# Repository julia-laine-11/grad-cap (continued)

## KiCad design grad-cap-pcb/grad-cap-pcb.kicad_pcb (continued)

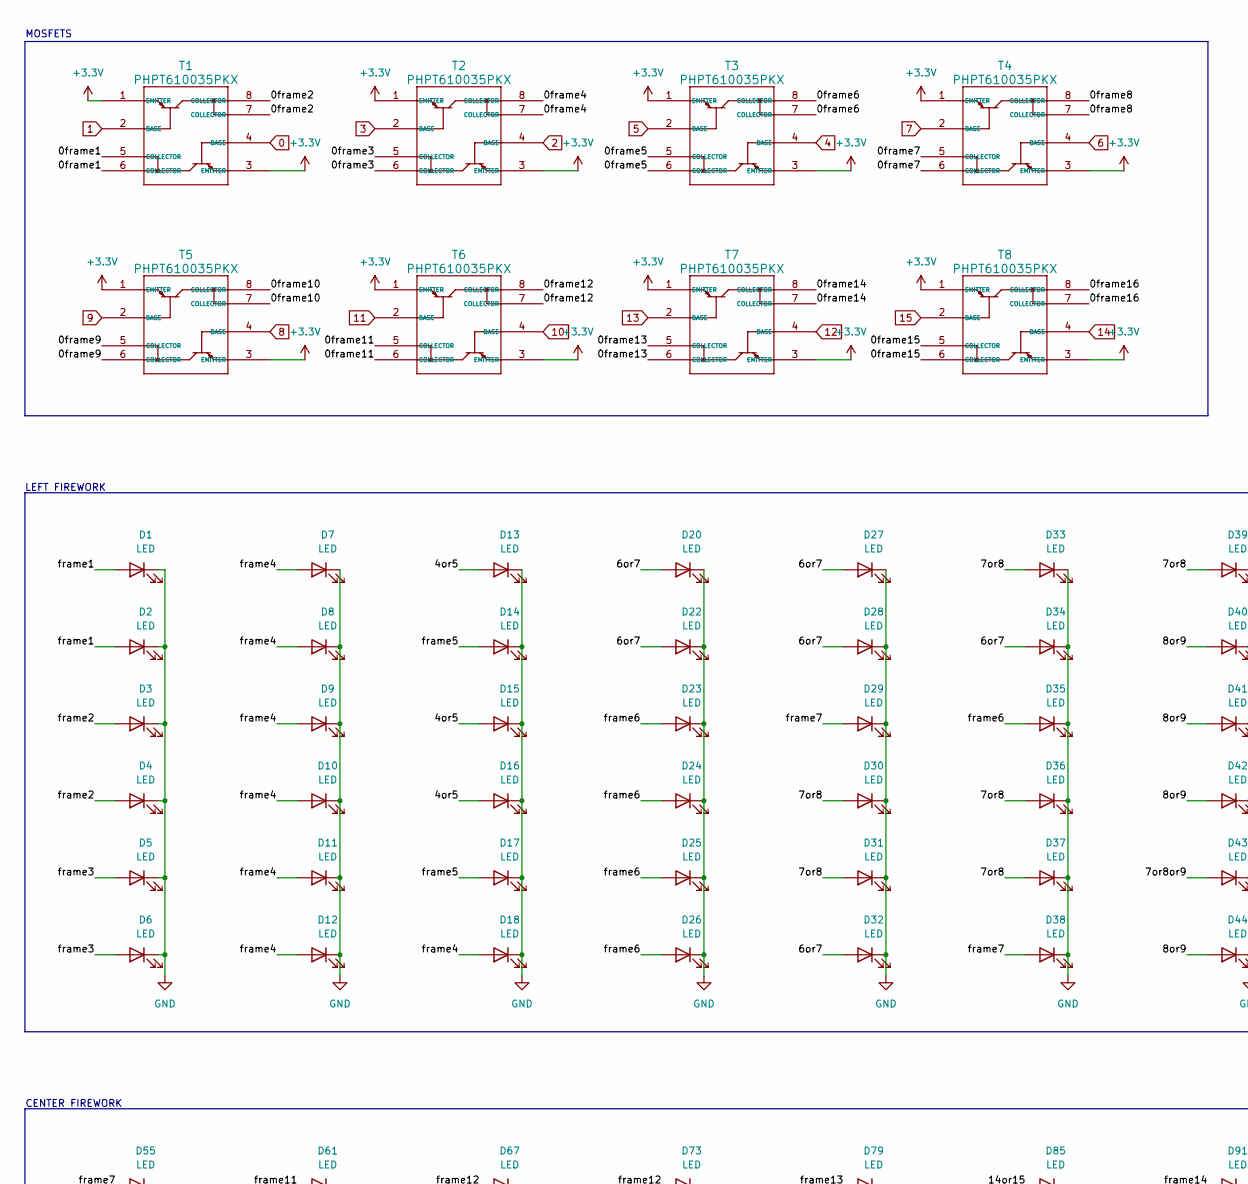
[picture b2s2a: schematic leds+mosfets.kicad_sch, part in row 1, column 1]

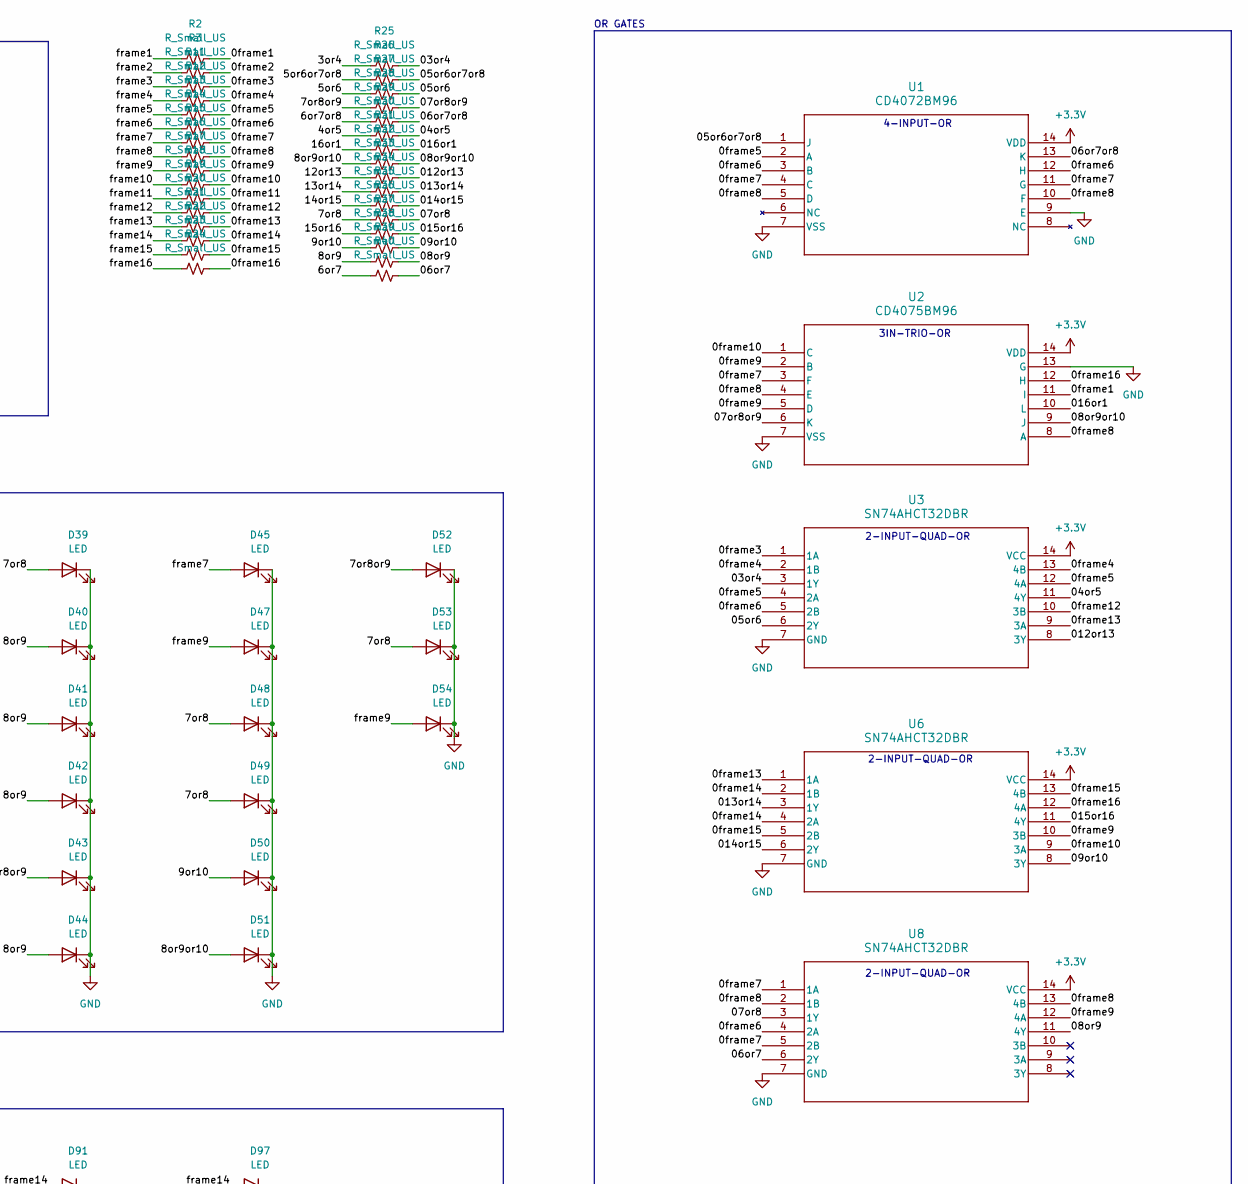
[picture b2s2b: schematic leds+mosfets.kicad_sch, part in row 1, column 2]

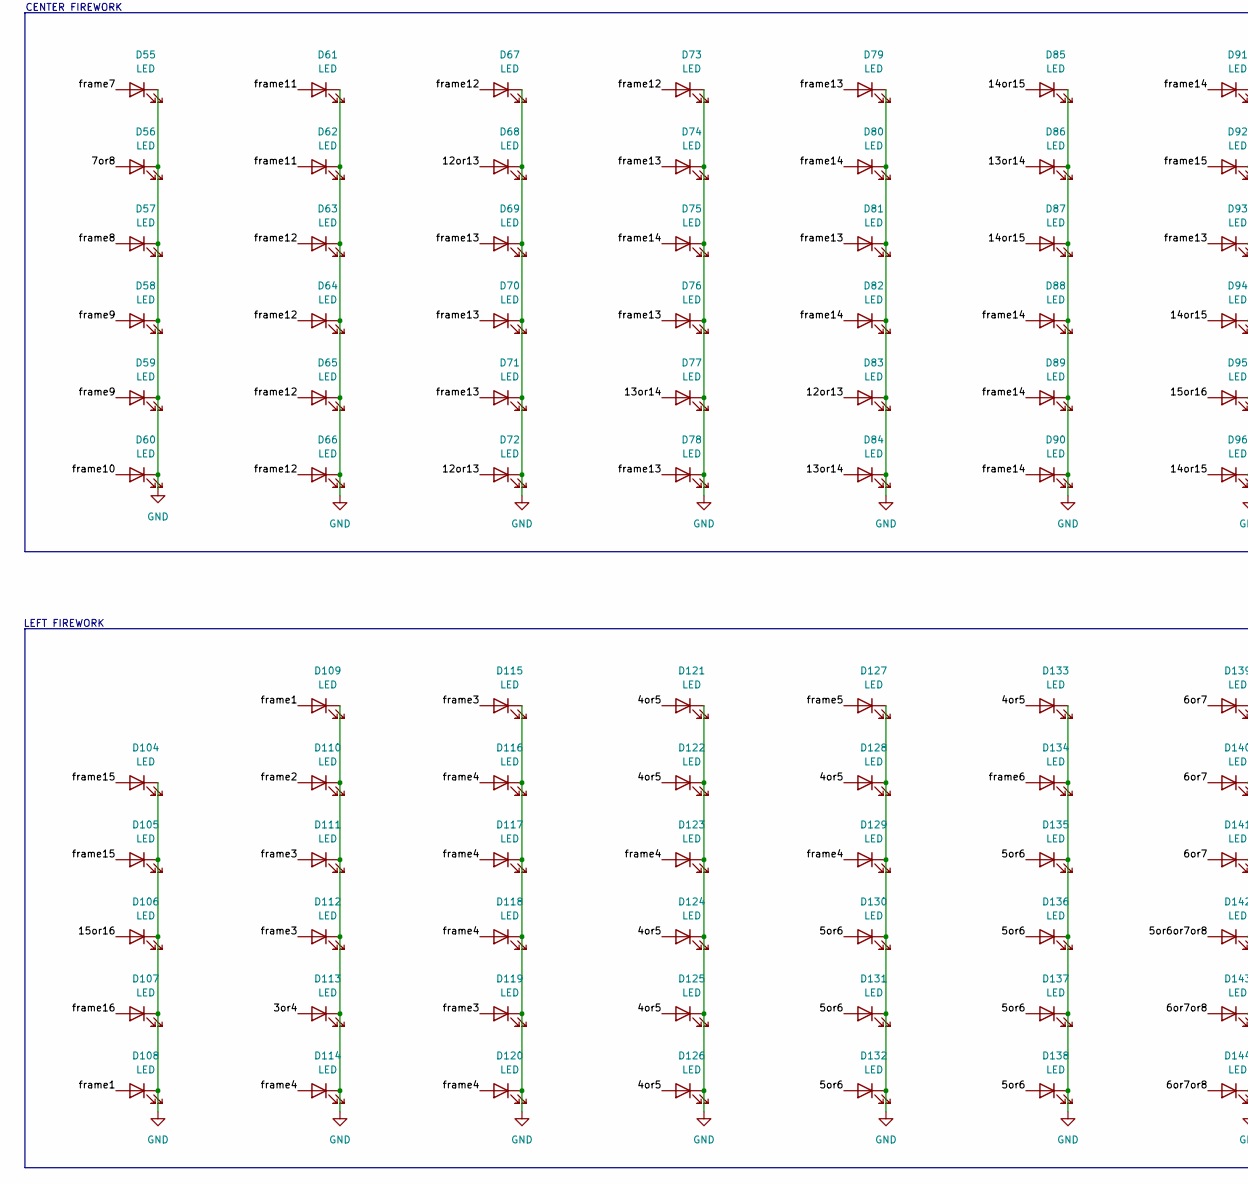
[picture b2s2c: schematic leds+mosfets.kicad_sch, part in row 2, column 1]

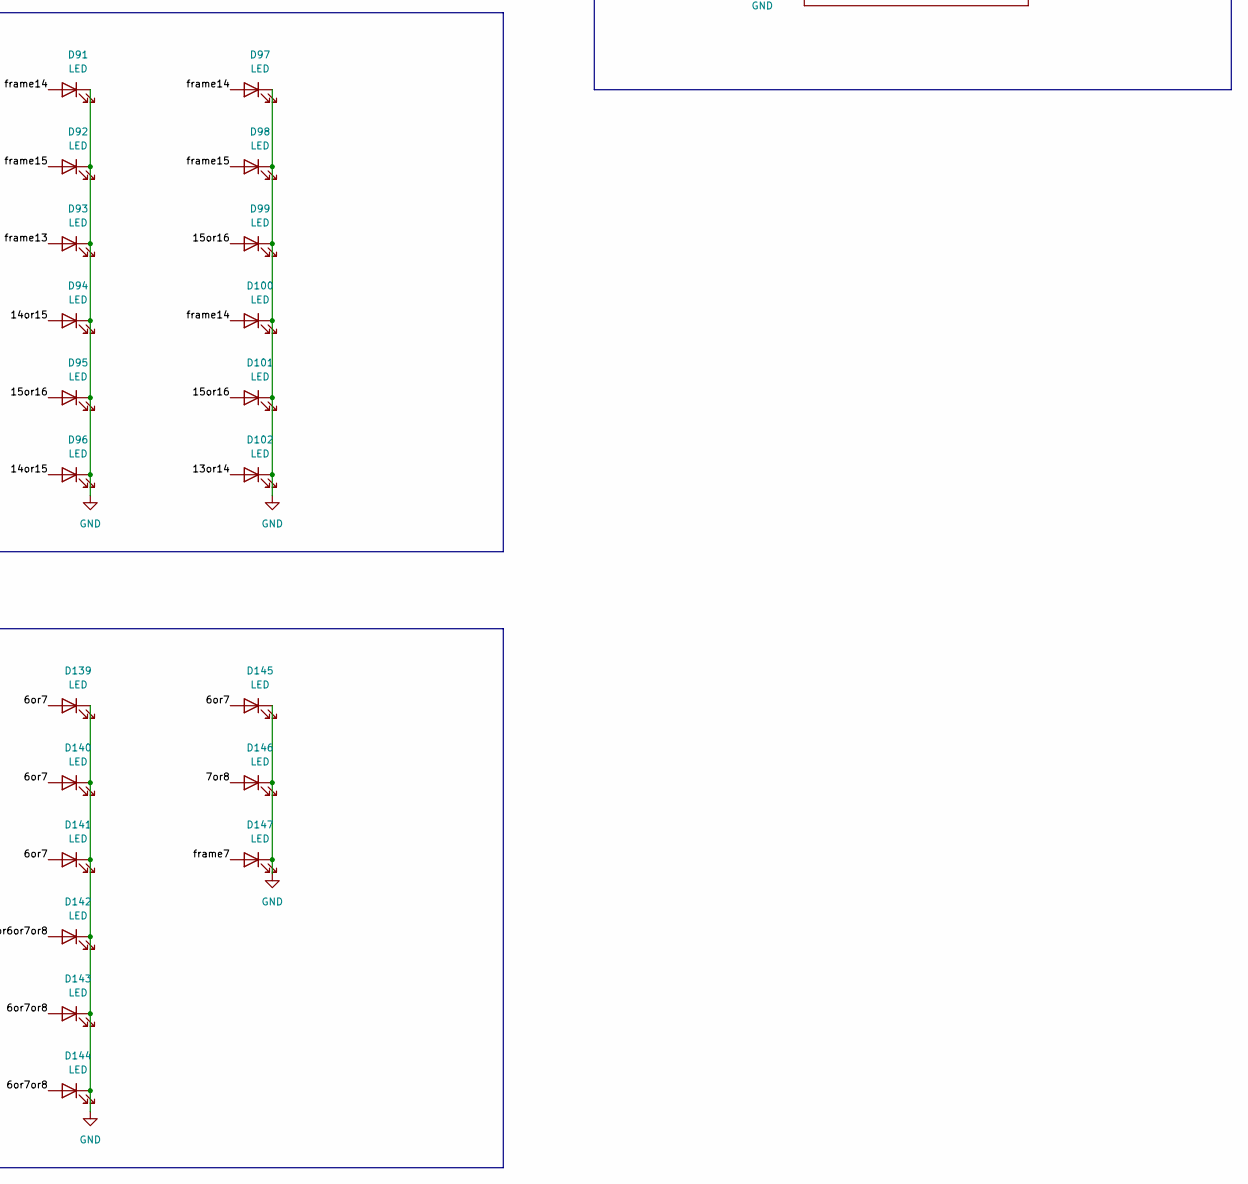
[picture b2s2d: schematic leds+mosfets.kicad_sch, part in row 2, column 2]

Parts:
D1, D2, D3, D4, D5, D6, D7, D8, D9, D10, D11, D12, D13, D14, D15, D16, D17, D18, D20, D22, D23, D24, D25, D26, D27, D28, D29, D30, D31, D32, D33, D34, D35, D36, D37, D38, D39, D40, D41, D42, D43, D44, D45, D47, D48, D49, D50, D51, D52, D53, D54, D55, D56, D57, D58, D59, D60, D61, D62, D63, D64, D65, D66, D67, D68, D69, D70, D71, D72, D73, D74, D75, D76, D77, D78, D79, D80, D81, D82, D83, D84, D85, D86, D87, D88, D89, D90, D91, D92, D93, D94, D95, D96, D97, D98, D99, D100, D101, D102, D104, D105, D106, D107, D108, D109, D110, D111, D112, D113, D114, D115, D116, D117, D118, D119, D120, D121, D122, D123, D124, D125, D126, D127, D128, D129, D130, D131, D132, D133, D134, D135, D136, D137, D138, D139, D140, D141, D142, D143, D144, D145, D146, D147: LED; LED_0603_1608Metric
R2, R3, R11, R12, R13, R14, R15, R16, R17, R18, R19, R20, R21, R22, R23, R24, R25, R26, R27, R28, R29, R30, R31, R32, R33, R34, R35, R36, R37, R38, R39, R40: R_Small_US; R_0805_2012Metric_Pad1.20x1.40mm_HandSolder
T1, T2, T3, T4, T5, T6, T7, T8: PHPT610035PKX; PHPT610035PKX_TRANS-2PNP-100V-3A
U1: CD4072BM96; CD4072BM96_4-INPUT-OR
U2: CD4075BM96; CD4075BM96-3IN-TRIO-OR
U3, U6, U8: SN74AHCT32DBR; SN74AHCT32DBR_2-INPUT-QUAD-OR

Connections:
0: T1.4 (BASE); also elsewhere on the board
1: T1.2 (BASE); also elsewhere on the board
2: T2.4 (BASE); also elsewhere on the board
3: T2.2 (BASE); also elsewhere on the board
4: T3.4 (BASE); also elsewhere on the board
5: T3.2 (BASE); also elsewhere on the board
6: T4.4 (BASE); also elsewhere on the board
7: T4.2 (BASE); also elsewhere on the board
8: T5.4 (BASE); also elsewhere on the board
9: T5.2 (BASE); also elsewhere on the board
10: T6.4 (BASE); also elsewhere on the board
11: T6.2 (BASE); also elsewhere on the board
12: T7.4 (BASE); also elsewhere on the board
13: T7.2 (BASE); also elsewhere on the board
14: T8.4 (BASE); also elsewhere on the board
15: T8.2 (BASE); also elsewhere on the board
+3.3V: T1.1 (EMITTER), T1.3 (EMITTER), T2.1 (EMITTER), T2.3 (EMITTER), T3.1 (EMITTER), T3.3 (EMITTER), T4.1 (EMITTER), T4.3 (EMITTER), T5.1 (EMITTER), T5.3 (EMITTER), T6.1 (EMITTER), T6.3 (EMITTER), T7.1 (EMITTER), T7.3 (EMITTER), T8.1 (EMITTER), T8.3 (EMITTER), U1.14 (VDD), U2.14 (VDD), U3.14 (VCC), U6.14 (VCC), U8.14 (VCC); also elsewhere on the board
/leds+mosfets/0frame1: R2.2, T1.5 (COLLECTOR), T1.6 (COLLECTOR), U2.11 (I)
/leds+mosfets/0frame2: R3.2, T1.7 (COLLECTOR), T1.8 (COLLECTOR)
/leds+mosfets/0frame3: R11.2, T2.5 (COLLECTOR), T2.6 (COLLECTOR), U3.1 (1A)
/leds+mosfets/0frame4: R12.2, T2.7 (COLLECTOR), T2.8 (COLLECTOR), U3.2 (1B), U3.13 (4B)
/leds+mosfets/0frame5: R13.2, T3.5 (COLLECTOR), T3.6 (COLLECTOR), U1.2 (A), U3.4 (2A), U3.12 (4A)
/leds+mosfets/0frame6: R14.2, T3.7 (COLLECTOR), T3.8 (COLLECTOR), U1.3 (B), U1.12 (H), U3.5 (2B), U8.4 (2A)
/leds+mosfets/0frame7: R15.2, T4.5 (COLLECTOR), T4.6 (COLLECTOR), U1.4 (C), U1.11 (G), U2.3 (F), U8.1 (1A), U8.5 (2B)
/leds+mosfets/0frame8: R16.2, T4.7 (COLLECTOR), T4.8 (COLLECTOR), U1.5 (D), U1.10 (F), U2.4 (E), U2.8 (A), U8.2 (1B), U8.13 (4B)
/leds+mosfets/0frame9: R17.2, T5.5 (COLLECTOR), T5.6 (COLLECTOR), U2.2 (B), U2.5 (D), U6.10 (3B), U8.12 (4A)
/leds+mosfets/0frame10: R18.2, T5.7 (COLLECTOR), T5.8 (COLLECTOR), U2.1 (C), U6.9 (3A)
/leds+mosfets/0frame11: R19.2, T6.5 (COLLECTOR), T6.6 (COLLECTOR)
/leds+mosfets/0frame12: R20.2, T6.7 (COLLECTOR), T6.8 (COLLECTOR), U3.10 (3B)
/leds+mosfets/0frame13: R21.2, T7.5 (COLLECTOR), T7.6 (COLLECTOR), U3.9 (3A), U6.1 (1A)
/leds+mosfets/0frame14: R22.2, T7.7 (COLLECTOR), T7.8 (COLLECTOR), U6.2 (1B), U6.4 (2A)
/leds+mosfets/0frame15: R23.2, T8.5 (COLLECTOR), T8.6 (COLLECTOR), U6.5 (2B), U6.13 (4B)
/leds+mosfets/0frame16: R24.2, T8.7 (COLLECTOR), T8.8 (COLLECTOR), U2.12 (H), U6.12 (4A)
/leds+mosfets/3or4: D113.2 (A), R25.1
/leds+mosfets/03or4: R25.2, U3.3 (1Y)
/leds+mosfets/4or5: D13.2 (A), D15.2 (A), D16.2 (A), D121.2 (A), D122.2 (A), D124.2 (A), D125.2 (A), D126.2 (A), D128.2 (A), D133.2 (A), R30.1
/leds+mosfets/04or5: R30.2, U3.11 (4Y)
/leds+mosfets/5or6: D130.2 (A), D131.2 (A), D132.2 (A), D135.2 (A), D136.2 (A), D137.2 (A), D138.2 (A), R27.1
/leds+mosfets/05or6: R27.2, U3.6 (2Y)
/leds+mosfets/5or6or7or8: D142.2 (A), R26.1
/leds+mosfets/05or6or7or8: R26.2, U1.1 (J)
/leds+mosfets/6or7: D20.2 (A), D22.2 (A), D27.2 (A), D28.2 (A), D32.2 (A), D34.2 (A), D139.2 (A), D140.2 (A), D141.2 (A), D145.2 (A), R40.1
/leds+mosfets/06or7: R40.2, U8.6 (2Y)
/leds+mosfets/6or7or8: D143.2 (A), D144.2 (A), R29.1
/leds+mosfets/06or7or8: R29.2, U1.13 (K)
/leds+mosfets/7or8: D30.2 (A), D31.2 (A), D33.2 (A), D36.2 (A), D37.2 (A), D39.2 (A), D48.2 (A), D49.2 (A), D53.2 (A), D56.2 (A), D146.2 (A), R36.1
/leds+mosfets/07or8: R36.2, U8.3 (1Y)
/leds+mosfets/7or8or9: D43.2 (A), D52.2 (A), R28.1
/leds+mosfets/07or8or9: R28.2, U2.6 (K)
/leds+mosfets/8or9: D40.2 (A), D41.2 (A), D42.2 (A), D44.2 (A), R39.1
/leds+mosfets/08or9: R39.2, U8.11 (4Y)
/leds+mosfets/8or9or10: D51.2 (A), R32.1
/leds+mosfets/08or9or10: R32.2, U2.9 (J)
/leds+mosfets/9or10: D50.2 (A), R38.1
/leds+mosfets/09or10: R38.2, U6.8 (3Y)
/leds+mosfets/012or13: R33.2, U3.8 (3Y)
/leds+mosfets/12or13: D68.2 (A), D72.2 (A), D83.2 (A), R33.1
/leds+mosfets/13or14: D77.2 (A), D84.2 (A), D86.2 (A), D102.2 (A), R34.1
/leds+mosfets/013or14: R34.2, U6.3 (1Y)
/leds+mosfets/14or15: D85.2 (A), D87.2 (A), D94.2 (A), D96.2 (A), R35.1
/leds+mosfets/014or15: R35.2, U6.6 (2Y)
/leds+mosfets/15or16: D95.2 (A), D99.2 (A), D101.2 (A), D106.2 (A), R37.1
/leds+mosfets/015or16: R37.2, U6.11 (4Y)
/leds+mosfets/016or1: R31.2, U2.10 (L)
/leds+mosfets/16or1: R31.1
/leds+mosfets/frame1: D1.2 (A), D2.2 (A), D108.2 (A), D109.2 (A), R2.1
/leds+mosfets/frame2: D3.2 (A), D4.2 (A), D110.2 (A), R3.1
/leds+mosfets/frame3: D5.2 (A), D6.2 (A), D111.2 (A), D112.2 (A), D115.2 (A), D119.2 (A), R11.1
/leds+mosfets/frame4: D7.2 (A), D8.2 (A), D9.2 (A), D10.2 (A), D11.2 (A), D12.2 (A), D18.2 (A), D114.2 (A), D116.2 (A), D117.2 (A), D118.2 (A), D120.2 (A), D123.2 (A), D129.2 (A), R12.1
/leds+mosfets/frame5: D14.2 (A), D17.2 (A), D127.2 (A), R13.1
/leds+mosfets/frame6: D23.2 (A), D24.2 (A), D25.2 (A), D26.2 (A), D35.2 (A), D134.2 (A), R14.1
/leds+mosfets/frame7: D29.2 (A), D38.2 (A), D45.2 (A), D55.2 (A), D147.2 (A), R15.1
/leds+mosfets/frame8: D57.2 (A), R16.1
/leds+mosfets/frame9: D47.2 (A), D54.2 (A), D58.2 (A), D59.2 (A), R17.1
/leds+mosfets/frame10: D60.2 (A), R18.1
/leds+mosfets/frame11: D61.2 (A), D62.2 (A), R19.1
/leds+mosfets/frame12: D63.2 (A), D64.2 (A), D65.2 (A), D66.2 (A), D67.2 (A), D73.2 (A), R20.1
/leds+mosfets/frame13: D69.2 (A), D70.2 (A), D71.2 (A), D74.2 (A), D76.2 (A), D78.2 (A), D79.2 (A), D81.2 (A), D93.2 (A), R21.1
/leds+mosfets/frame14: D75.2 (A), D80.2 (A), D82.2 (A), D88.2 (A), D89.2 (A), D90.2 (A), D91.2 (A), D97.2 (A), D100.2 (A), R22.1
/leds+mosfets/frame15: D92.2 (A), D98.2 (A), D104.2 (A), D105.2 (A), R23.1
/leds+mosfets/frame16: D107.2 (A), R24.1
GND: D1.1 (K), D2.1 (K), D3.1 (K), D4.1 (K), D5.1 (K), D6.1 (K), D7.1 (K), D8.1 (K), D9.1 (K), D10.1 (K), D11.1 (K), D12.1 (K), D13.1 (K), D14.1 (K), D15.1 (K), D16.1 (K), D17.1 (K), D18.1 (K), D20.1 (K), D22.1 (K), D23.1 (K), D24.1 (K), D25.1 (K), D26.1 (K), D27.1 (K), D28.1 (K), D29.1 (K), D30.1 (K), D31.1 (K), D32.1 (K), D33.1 (K), D34.1 (K), D35.1 (K), D36.1 (K), D37.1 (K), D38.1 (K), D39.1 (K), D40.1 (K), D41.1 (K), D42.1 (K), D43.1 (K), D44.1 (K), D45.1 (K), D47.1 (K), D48.1 (K), D49.1 (K), D50.1 (K), D51.1 (K), D52.1 (K), D53.1 (K), D54.1 (K), D55.1 (K), D56.1 (K), D57.1 (K), D58.1 (K), D59.1 (K), D60.1 (K), D61.1 (K), D62.1 (K), D63.1 (K), D64.1 (K), D65.1 (K), D66.1 (K), D67.1 (K), D68.1 (K), D69.1 (K), D70.1 (K), D71.1 (K), D72.1 (K), D73.1 (K), D74.1 (K), D75.1 (K), D76.1 (K), D77.1 (K), D78.1 (K), D79.1 (K), D80.1 (K), D81.1 (K), D82.1 (K), D83.1 (K), D84.1 (K), D85.1 (K), D86.1 (K), D87.1 (K), D88.1 (K), D89.1 (K), D90.1 (K), D91.1 (K), D92.1 (K), D93.1 (K), D94.1 (K), D95.1 (K), D96.1 (K), D97.1 (K), D98.1 (K), D99.1 (K), D100.1 (K), D101.1 (K), D102.1 (K), D104.1 (K), D105.1 (K), D106.1 (K), D107.1 (K), D108.1 (K), D109.1 (K), D110.1 (K), D111.1 (K), D112.1 (K), D113.1 (K), D114.1 (K), D115.1 (K), D116.1 (K), D117.1 (K), D118.1 (K), D119.1 (K), D120.1 (K), D121.1 (K), D122.1 (K), D123.1 (K), D124.1 (K), D125.1 (K), D126.1 (K), D127.1 (K), D128.1 (K), D129.1 (K), D130.1 (K), D131.1 (K), D132.1 (K), D133.1 (K), D134.1 (K), D135.1 (K), D136.1 (K), D137.1 (K), D138.1 (K), D139.1 (K), D140.1 (K), D141.1 (K), D142.1 (K), D143.1 (K), D144.1 (K), D145.1 (K), D146.1 (K), D147.1 (K), U1.7 (VSS), U1.9 (E), U2.7 (VSS), U2.13 (G), U3.7 (GND), U6.7 (GND), U8.7 (GND); also elsewhere on the board

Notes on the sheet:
LEFT FIREWORK
OR GATES
4-INPUT-OR
CENTER FIREWORK
3IN-TRIO-OR
2-INPUT-QUAD-OR
MOSFETS

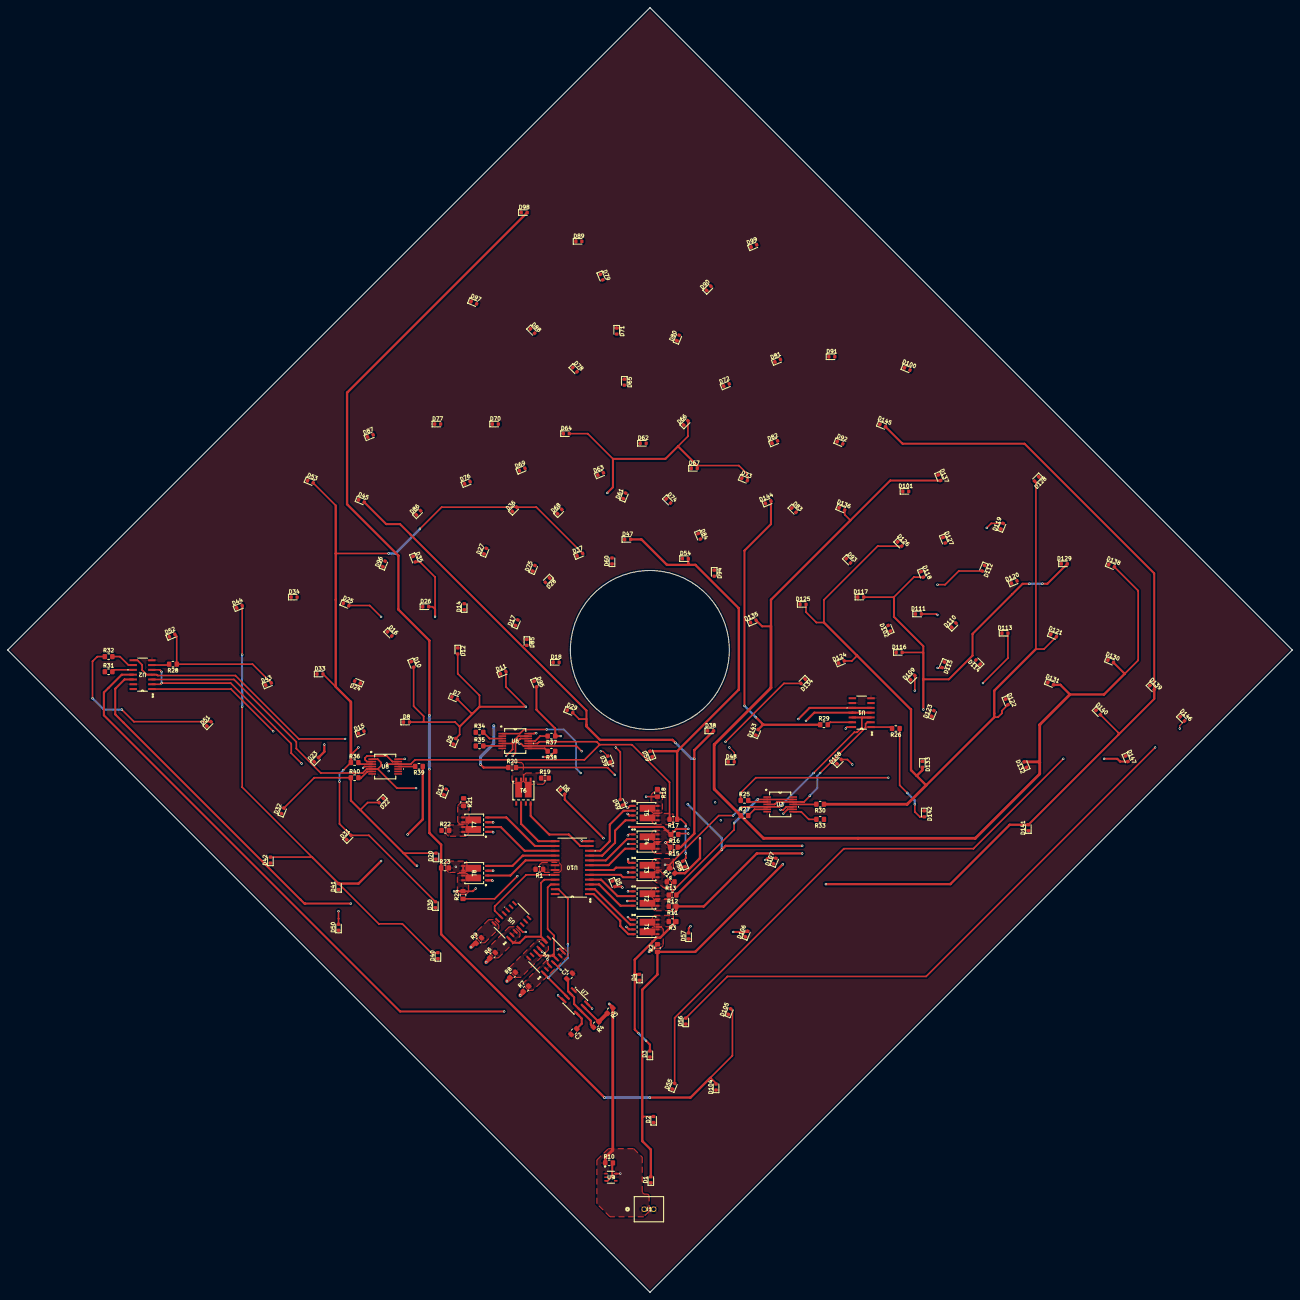
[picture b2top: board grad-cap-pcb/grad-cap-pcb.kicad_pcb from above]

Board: 4 copper layers, 339.4 x 339.4 mm, 204 parts (0 on the bottom side), 94 nets.

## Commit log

2026-01-11 laid out leds
2026-01-12 detail out readme
2026-01-12 added led sequence chart
2026-01-12 added animation
2026-01-13 addd more
    switched from npn to pnp to make the LEDs connect to the ground plane - easier routing.
    added labels and or gates so the mosfets wouldnt trigger each other
2026-01-14 added many things
    added: mux
    counter
    signal gen - still needs r1 and r2 values
    power management
    kicad symbol library - footprints not assigned
2026-01-14 edited layout
2026-01-21 routed traces, added resistors
2026-01-21 screw it were making it 8 frames, 16 is too mcuh
2026-01-27 added 8 frame option + updated power supply
    - i was having trouble with the 4 layer since it would be expensive to make and it also had a loottttt of traces.
    - added resistor per led because im not sure what i was on when i decided i only needed 1 resistor per frame.
    - changed the tails to white instead of the same color by popular vote of my friends
    - removed 3v7 -> 2v1 converter
2026-01-28 update readme due to large changes
    Reduced LED frames from 16 to 8 for easier routing and manufacturing. Updated hardware details and pulse generation options.
2026-01-28 Revise LED colors and frame count in README
    Updated LED specifications and reduced frame count for fireworks.
2026-02-08 routed traces, reorganized, renamed
2026-02-10 reorganized
    horizontal -> vertical pin headers
    traces added
    moved components
    switched clocks crystal-> si
2026-02-12 updated pcb
    error checking
    90* angles removal
    schematic relinking
    reorganizing schematic
    fixed footprints for PHPT6 (mosfets, they didnt like the pads and the body being "different" pours or something)
    silkscreen reorg
2026-02-12 removed old files
    i am no longer using the 16 frame cap and the initial try of the 8 frame cap was too boring. removing these files for clarity
2026-02-13 updated pcb
    shrunk edge cuts
    moved led matrix header (again)
    added 3d file links
    added mounting holes
    added 3 on board buttons
    fixed unused pin header connections
2026-02-13 updated silkscreen
    added custom designs
    - put them to the side
    lowkey cant decide what to do with them, or if i put them at all
2026-02-23 Revise hardware details and add PCB images
    Updated hardware section with new components and configurations. Added PCB images and silkscreen options.
2026-03-09 update readme
    - prototyping
    - pcb update
    - schematic update
2026-03-09 updated from prototyping
    - jk ff -> incrementer
    - shrink to be cap size
    - rename labels to match layout
2026-03-18 updated pcb
    added labels for each diode
    changed silkscreen to be handwriting
2026-03-30 final push
2026-04-09 final push
    inverters for pmos
    resistors for mux
    silkscreen looking fire as hell honestly
